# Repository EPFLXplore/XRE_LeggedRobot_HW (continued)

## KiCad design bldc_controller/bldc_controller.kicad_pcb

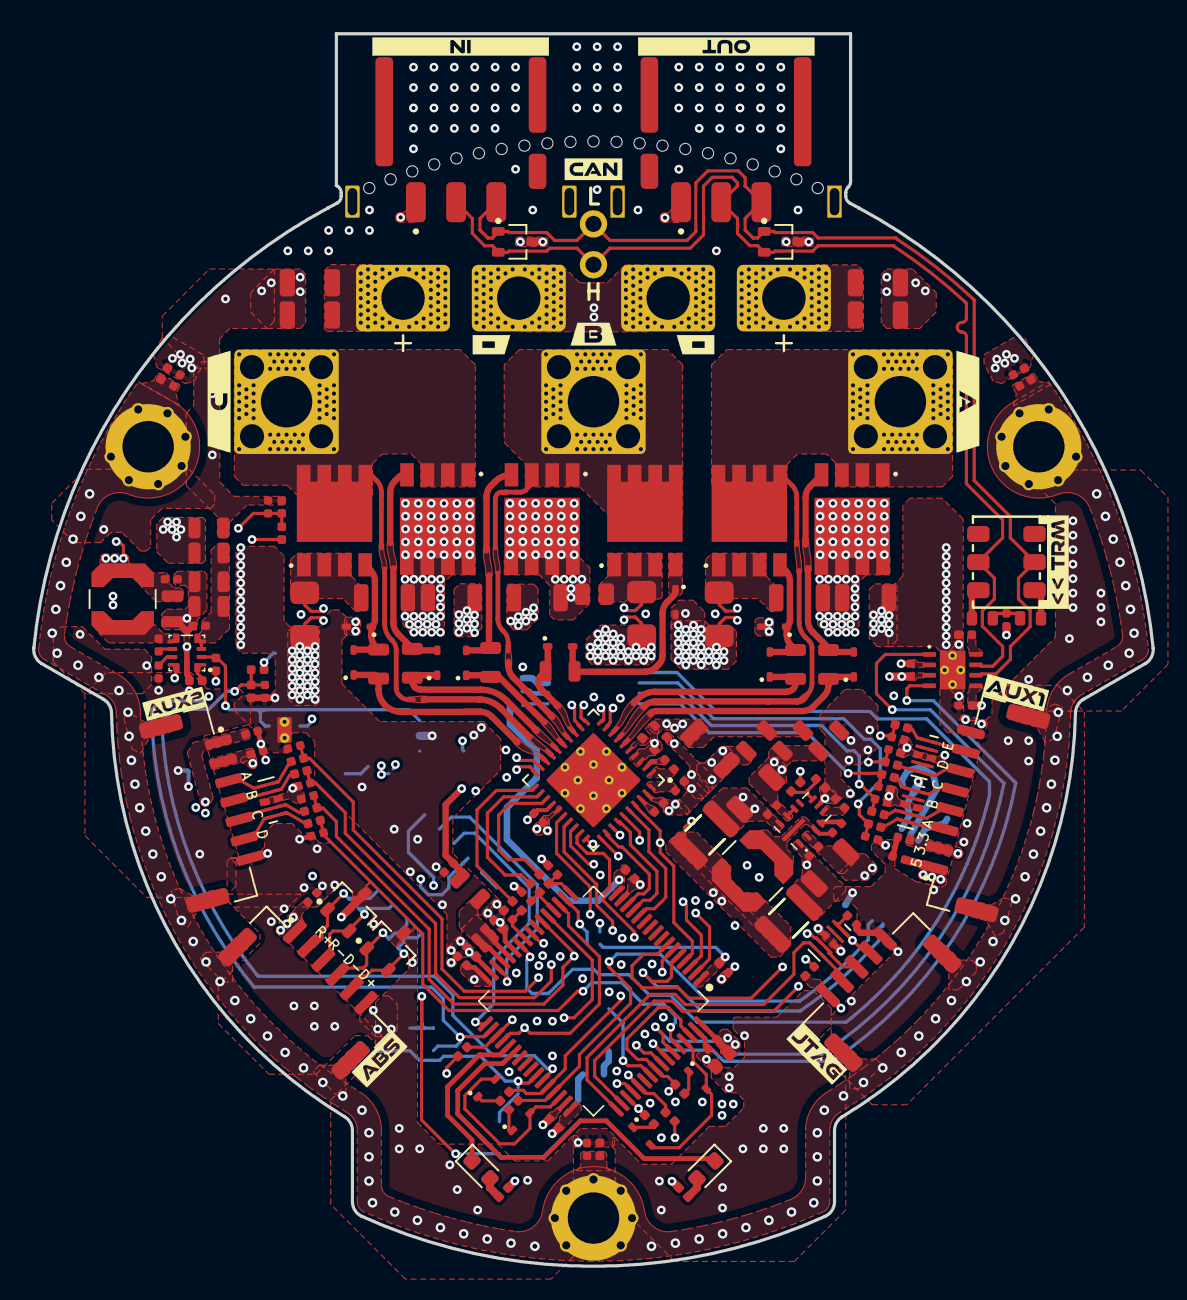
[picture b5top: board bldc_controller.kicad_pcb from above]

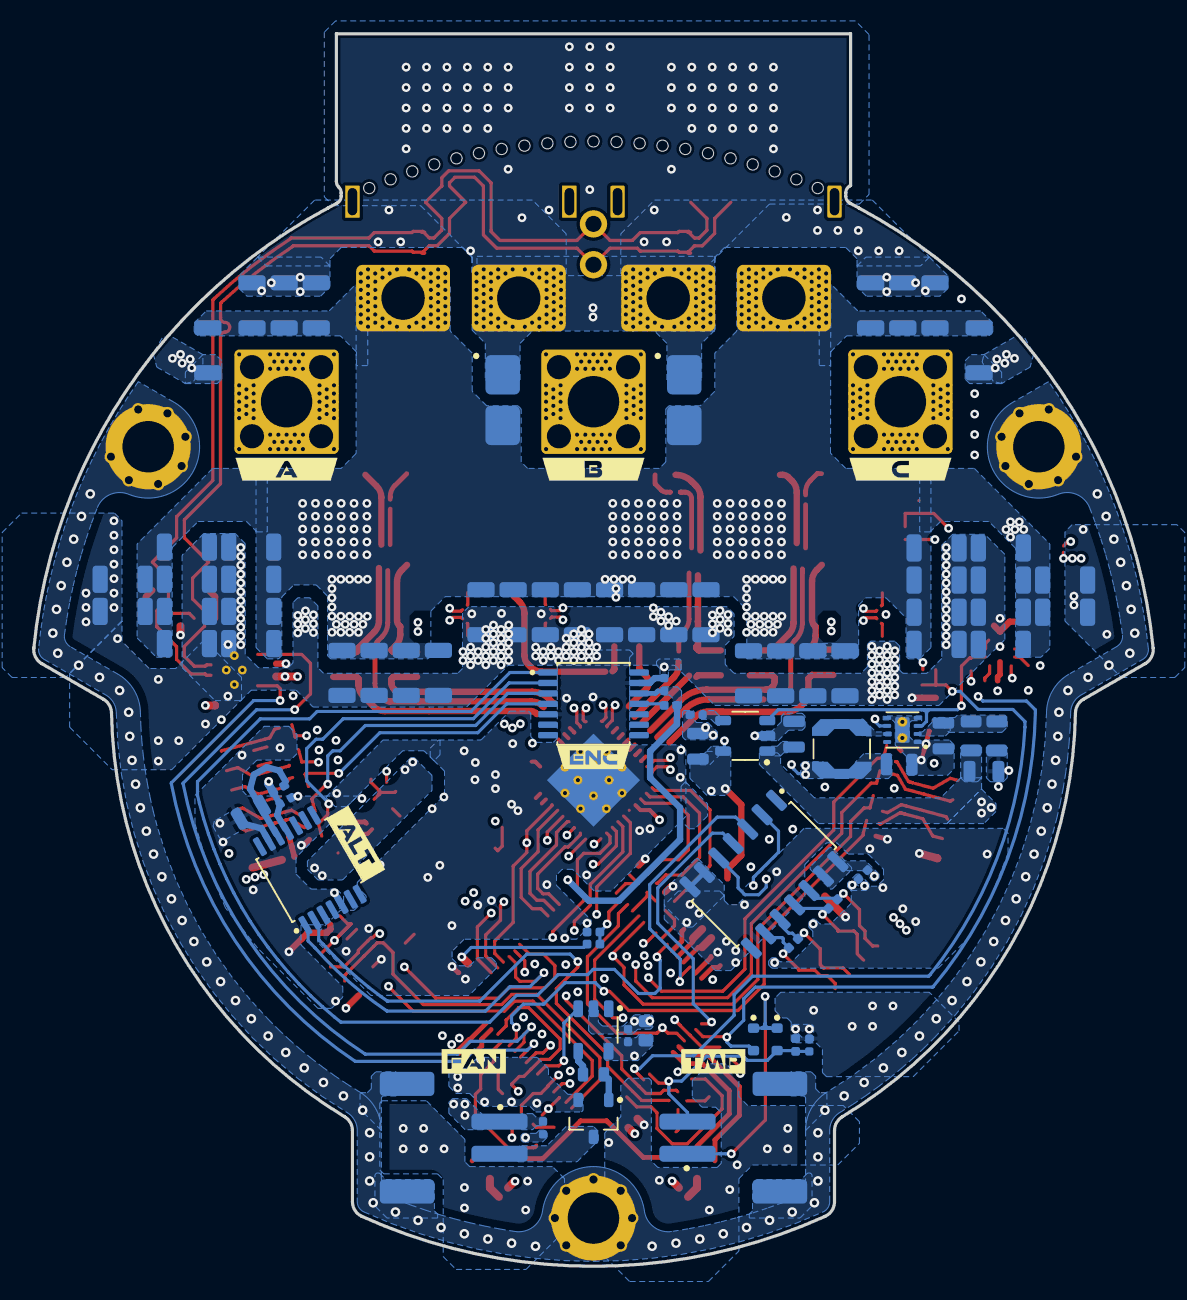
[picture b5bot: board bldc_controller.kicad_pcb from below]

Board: 6 copper layers, 69.7 x 76.7 mm, 287 parts (94 on the bottom side), 131 nets.

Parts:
C1, C103: 4u7 X7R 25V; C_0603_1608_DensityHigh
C2, C3, C6, C8, C9, C10, C54, C58, C79, C80, C94, C95, C96, C98, C99, C100, C101, C102, C104, C105, C106, C107, C108, C118, C123, C131, C132: 100n X7R 100V; C_0402_1005_DensityHigh
C4, C7, C33, C41, C130: 1u X7R 100V; C_0402_1005_DensityHigh
C5, C119: 4u7 X7R 25V; C_0402_1005_DensityHigh
C11, C12, C13: 1n X7R 25V; C_0402_1005_DensityHigh
C14, C15, C16, C18, C19, C20, C21, C22, C23, C24, C25, C26, C27, C28, C30, C31, C32, C34, C35, C36, C38, C39, C40, C42, C43, C44, C45, C46, C47, C48, C49, C50, C51, C52, C53, C55, C56, C57, C59, C60, C61, C63, C64, C65, C66, C67, C68, C70, C71, C72: 4u7 X7R 100V; C_1206_3216_DensityHigh
C17, C124, C125, C126, C127, C128, C129: 2u2 X7R 100V; R_0805_2012_DensityHigh
C29, C37: 220n X7R 100V; C_0402_1005_DensityHigh
C62, C74, C77, C97: 10u X7R 6.3V; C_0805_2012_DensityHighest
C69, C73: 15u X7R 25V; C_1210_3225_DensityHigh
C75: 10u X7R 25V; C_0805_2012_DensityHighest
C76: 10n X7R 25V; C_0402_1005_DensityHigh
C78: 22u X7R 10V; C_0805_2012_DensityHighest
C81: 1u X7R 25V; C_0402_1005_DensitySpaced
C82, C89, C91, C93: 4u7 X7R 100V; C_1206_3216_DensityHighest
C83: 100n X7R 16V; C_0402_1005_DensityHigh
C84: 47n X7R 100V; C_0402_1005_DensityHigh
C85: 100n X7R 100V; C_0402_1005_DensitySpaced
C86: 1u X7R 25V; C_0402_1005_DensityHigh
C87: 1u X7R 16V; C_0402_1005_DensityHigh
C88, C92: 100n X7R 100V; C_1206_3216_DensityHighest
C90: 100n X7R 100V; C_0805_2012_DensityHigh
C109, C110, C111, C112, C113, C114, C115, C116, C117: DNP; C_0402_1005_DensityHigh
C120, C121, C122: 330n X7R 100V; C_0402_1005_DensityHigh
D1, D2, D3, D4, D5, D6, D7, D8, D9, D12, D13, D17, D18, D19, D20: BAT41KFILM; D_SOD-523
D10, D11: GREEN; LED_0603_1608Metric
D14, D15: PESD4USB5B-TTSX; DFN2510-D10
D16, D24: PESD4USB3U-TTSX; DFN2510-D10
D21, D25: CDSOT23-SM712; SOT95P230X117-3N
D22, D23: PESD2CANFD24V-UX; SOT95P230X117-3N
FB1, FB2, FB3, FB4: 1k @ 100MHz; R_0805_2012_DensityHigh
H1, H2, H3: M3; MountingHole_3.2mm_M3_Pad_Via
J1: XT60PW-F; AMASS_XT60PW-F_1x02_P7.20mm_Horizontal
J2: XT60PW-M; AMASS_XT60PW-M_1x02_P7.20mm_Horizontal
J3: Phase A; Pad_Square_Vias_6.5x6.5mm
J4: Phase B; Pad_Square_Vias_6.5x6.5mm
J5: Phase C; Pad_Square_Vias_6.5x6.5mm
J6: SM08B-GHS-TB; JST_GH_SM08B-GHS-TB_1x08-1MP_P1.25mm_Horizontal
J7: SM07B-GHS-TB; JST_GH_SM07B-GHS-TB_1x07-1MP_P1.25mm_Horizontal
J8, J10: JST S2B-PH-SM4-TB; JST_PH_S2B-PH-SM4-TB_1x02-1MP_P2.00mm_Horizontal
J9: SM06B-GHS-TB; JST_GH_SM06B-GHS-TB_1x06-1MP_P1.25mm_Horizontal
J11, J12: Nano-Fit 1x03; 1054301203
J13: SM05B-GHS-TB; JST_GH_SM05B-GHS-TB_1x05-1MP_P1.25mm_Horizontal
J14: PTH 01x02 2.54mm; PTH_1x02_P2.54mm
L1, L2: 22u; L_Coilcraft_LPS4018
L3: 2u2; L_Coilcraft_LPS3314
NT1: FB_5V; NetTie-2_SMD_Pad0.2mm
NT2: FB_12V; NetTie-2_SMD_Pad0.2mm
NT3: VOS_3V3; NetTie-2_SMD_Pad0.2mm
NT4: SRC_HS_A; NetTie-2_SMD_Pad0.3mm
NT5: SHNTA_P; NetTie-2_SMD_Pad0.2mm
NT6: SHNTA_N; NetTie-2_SMD_Pad0.2mm
NT7: SRC_HS_B; NetTie-2_SMD_Pad0.3mm
NT8: SHNTB_P; NetTie-2_SMD_Pad0.2mm
NT9: SHNTB_N; NetTie-2_SMD_Pad0.2mm
NT10: SRC_HS_C; NetTie-2_SMD_Pad0.3mm
NT11: SHNTC_P; NetTie-2_SMD_Pad0.2mm
NT12: SHNTC_N; NetTie-2_SMD_Pad0.2mm
NT13: NTC_MOT_H; NetTie-2_SMD_Pad0.2mm
NT14: NTC_MOT_L; NetTie-2_SMD_Pad0.2mm
Q1, Q2, Q3, Q4, Q5, Q6: TPW1R306PL,L1Q; 2-5S1A
Q7: PMV15ENER; SOT95P230X110-3N
R1, R2, R3: 22R 1%; R_0402_1005_DensityHigh
R4, R26, R27, R47, R48, R49: 0R; R_0402_1005_DensityHigh
R5, R18, R24: 100k 1%; R_0402_1005_DensityHigh
R6: 9k09 1%; R_0402_1005_DensityHigh
R7, R8, R39, R40, R41, R42: 2k 1%; R_0402_1005_DensityHigh
R9, R10, R12, R13, R15, R16: 7R5 1%; R_0805_2012_DensityHigh
R11, R14, R17: 0m5 1% 2W; HCS1206FTL500
R19: DNP; R_0402_1005_DensityHigh
R20, R21: 560R 1%; R_0402_1005_DensityHigh
R22, R23, R28, R50: 10k 1%; R_0402_1005_DensityHigh
R25: 4.7k 1%; R_0402_1005_DensityHigh
R29: 10R 1%; R_0603_1608_DensityHigh
R30, R31, R32, R33, R34, R35, R36, R37, R38, R45, R46: 100R 1%; R_0402_1005_DensityHigh
R43, R44: 60R4 1% 1/4W; R_0603_1608_DensityHigh
SW1: CAS-220TA; CAS-220A_NDC-L
TH1: 47k 1% NTC; R_0402_1005_DensityHigh
U1: STM32G474RET3; LQFP-64_10x10mm_P0.5mm
U2: LMR36503MSC5RPERQ1; LMR36503
U3: LMR36006FSCQRNXRQ1
U4: TPS62172DSG; WSON-8-1EP_2x2mm_P0.5mm_EP0.9x1.6mm_ThermalVias
U5: LP2992IM5-3.3/NOPB; SOT95P280X145-5N
U6, U7: SMBJ51CD-M3/H; DIOM4336X24N
U8: DRV8353FS; WQFN-40-1EP_6x6mm_P0.5mm_EP4.15x4.15mm_ThermalVias
U9: AS5047P; SOP-14_4.4x5mm_P0.65mm_H1.2mm
U10: AS5048B; SOP-14_4.4x5mm_P0.65mm_H1.2mm
U11: SN65HVD35DR; SOIC-14 5.4mm
U12: TCAN1051HGVDRBRQ1; HVSON-8-1EP_3x3mm_P0.65mm_EP1.6x2.4mm_ThermalVias
U13: DGD0216WT-7; SOT-23-5
kibuzzard-657CD0A3: G***; kibuzzard-657CD0A3
kibuzzard-657CD0D0: G***; kibuzzard-657CD0D0
kibuzzard-657CD4CA: G***; kibuzzard-657CD4CA
kibuzzard-657CD4F2: G***; kibuzzard-657CD4F2
kibuzzard-657CD16C: G***; kibuzzard-657CD16C
kibuzzard-657CD27C: G***; kibuzzard-657CD27C
kibuzzard-657CD133: G***; kibuzzard-657CD133
kibuzzard-657CD374: G***; kibuzzard-657CD374
kibuzzard-657CE6B7: G***; kibuzzard-657CE6B7
kibuzzard-657CE6F4: G***; kibuzzard-657CE6F4
kibuzzard-657CE8E9: G***; kibuzzard-657CE8E9
kibuzzard-657CE8F0: G***; kibuzzard-657CE8F0
kibuzzard-657CE9A0: G***; kibuzzard-657CE9A0
kibuzzard-657CE9CF: G***; kibuzzard-657CE9CF
kibuzzard-657CE95C: G***; kibuzzard-657CE95C
kibuzzard-657CE353: G***; kibuzzard-657CE353
kibuzzard-657CE701: G***; kibuzzard-657CE701
kibuzzard-657CE738: G***; kibuzzard-657CE738
kibuzzard-657CEA4F: G***; kibuzzard-657CEA4F
kibuzzard-657CEA6A: G***; kibuzzard-657CEA6A

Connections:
+3V3: C1.1, C2.1, C3.1, C6.1, C7.1, C9.1, C78.1, C79.1, C80.1, C99.1, C100.1, C101.1, C107.1, C108.1, J6.2, J7.2, J13.1, L3.2, NT3.2, R7.1, R8.1, R18.1, R20.1, R21.1, R26.1, R27.1, U1.1 (VBAT), U1.16 (VDD), U1.32 (VDD), U1.48 (VDD), U1.64 (VDD), U9.12 (VDD3V3), U10.11 (VDD5V), U11.13 (VCC), U11.14 (VCC), U12.5 (VIO)
+5V: C54.1, C62.1, C74.1, C98.1, C102.1, C103.1, C104.1, C105.1, C106.1, C125.1, FB3.1, J6.1, J7.1, J9.1, L1.2, NT1.1, R50.2, U5.1 (VIN), U12.3 (VCC), U13.5 (VCC)
+12V: C69.1, C73.1, C123.1, J10.1, L2.2, NT2.2
+A3V3: C77.1, C83.1, C130.1, D12.1 (K), D13.1 (K), FB4.1, NT13.1, TH1.1, U5.5 (VOUT), U8.24 (VREF)
+VBAT: C14.1, C15.1, C16.1, C19.1, C20.1, C21.1, C22.1, C23.1, C24.1, C26.1, C27.1, C28.1, C30.1, C31.1, C32.1, C34.1, C35.1, C36.1, C38.1, C39.1, C40.1, C42.1, C43.1, C44.1, C45.1, C46.1, C47.1, C48.1, C49.1, C50.1, C51.1, C52.1, C53.1, C55.1, C56.1, C57.1, C59.1, C60.1, C61.1, C63.1, C64.1, C65.1, C66.1, C67.1, C68.1, C70.1, C71.1, C72.1, C81.1, C82.1, C85.1, C88.1, C89.1, C90.1, C91.1, C92.1, C93.1, C127.1, C128.1, FB1.1, FB2.1, J1.2, J2.2, Q1.5 (D), Q1.6 (D), Q1.7 (D), Q1.8 (D), Q3.5 (D), Q3.6 (D), Q3.7 (D), Q3.8 (D), Q5.5 (D), Q5.6 (D), Q5.7 (D), Q5.8 (D), R24.1, U6.2 (A2), U7.2 (A2), U8.3 (VM), U8.4 (VDRAIN)
/Project Architecture/Interface - FD-CAN/FDCAN_N: D22.1 (K1), D23.1 (K1), J11.3, J12.3, J14.2, SW1.2 (B), U12.6 (CANL)
/Project Architecture/Interface - FD-CAN/FDCAN_P: D22.2 (K2), D23.2 (K2), J11.2, J12.2, J14.1, SW1.5 (B), U12.7 (CANH)
/Project Architecture/Interface - FD-CAN/FDCAN_RX: U1.58 (PB5), U12.4 (RXD)
/Project Architecture/Interface - FD-CAN/FDCAN_S: R28.1, U12.8 (S)
/Project Architecture/Interface - FD-CAN/FDCAN_TX: U1.59 (PB6), U12.1 (TXD)
/Project Architecture/Interface - Fan Control/FAN_GATE: Q7.1 (G), R29.2
/Project Architecture/Interface - Fan Control/FAN_OUT: R29.1, U13.4 (OUT)
/Project Architecture/Interface - Fan Control/FAN_SW: J10.2, Q7.3 (D)
/Project Architecture/Interface - Interconnects/AUX1P_A: D16.5 (K), D16.6 (K), J6.3, R30.1
/Project Architecture/Interface - Interconnects/AUX1P_B: D16.4 (K), D16.7 (K), J6.4, R31.1
/Project Architecture/Interface - Interconnects/AUX1P_C: D16.1 (K), D16.10 (K), J6.5, R32.1
/Project Architecture/Interface - Interconnects/AUX1P_D: D14.5 (K), D14.6 (K), J6.6, R33.1
/Project Architecture/Interface - Interconnects/AUX1P_E: D14.1 (K), D14.10 (K), J6.7, R34.1
/Project Architecture/Interface - Interconnects/AUX1_A: C117.1, R30.2, U1.19 (PA5), U1.36 (PB14), U9.2 (CLK)
/Project Architecture/Interface - Interconnects/AUX1_B: C115.1, R31.2, U1.57 (PB4), U9.3 (MISO)
/Project Architecture/Interface - Interconnects/AUX1_C: C113.1, R32.2, U1.21 (PA7), U9.4 (MOSI)
/Project Architecture/Interface - Interconnects/AUX1_D: C111.1, R33.2, R39.2, U1.51 (PA15), U11.2 (R)
/Project Architecture/Interface - Interconnects/AUX1_D_K: D17.1 (K), R39.1
/Project Architecture/Interface - Interconnects/AUX1_E: C109.1, R34.2, R41.2, U1.56 (PB3), U1.62 (PB9), U11.5 (D)
/Project Architecture/Interface - Interconnects/AUX1_E_K: D19.1 (K), R41.1
/Project Architecture/Interface - Interconnects/AUX1_I2C_PULLUP: D17.2 (A), D19.2 (A), U1.61 (PB8)
/Project Architecture/Interface - Interconnects/AUX2P_A: D15.5 (K), D15.6 (K), J7.3, R35.1
/Project Architecture/Interface - Interconnects/AUX2P_B: D15.4 (K), D15.7 (K), J7.4, R36.1
/Project Architecture/Interface - Interconnects/AUX2P_C: D15.2 (K), D15.9 (K), J7.5, R37.1
/Project Architecture/Interface - Interconnects/AUX2P_D: D15.1 (K), D15.10 (K), J7.6, R38.1
/Project Architecture/Interface - Interconnects/AUX2_A: C116.1, R35.2, U1.6 (PF1)
/Project Architecture/Interface - Interconnects/AUX2_B: C114.1, R36.2, R40.2, U1.5 (PF0), U1.44 (PA10), U10.1 (SDA)
/Project Architecture/Interface - Interconnects/AUX2_B_K: D18.1 (K), R40.1
/Project Architecture/Interface - Interconnects/AUX2_C: C112.1, R37.2, R42.2, U1.22 (PC4), U1.45 (PA11), U10.2 (SCL)
/Project Architecture/Interface - Interconnects/AUX2_C_K: D20.1 (K), R42.1
/Project Architecture/Interface - Interconnects/AUX2_D: C110.1, R38.2, U1.60 (PB7)
/Project Architecture/Interface - Interconnects/AUX2_I2C_PULLUP: D18.2 (A), D20.2 (A), U1.46 (PA12)
/Project Architecture/Interface - Interconnects/CAN_TERM_B: R44.2, SW1.4 (A)
/Project Architecture/Interface - Interconnects/CAN_TERM_MID: C119.1, R43.2, R44.1
/Project Architecture/Interface - Interconnects/CAN_TERM_T: R43.1, SW1.1 (A)
/Project Architecture/Interface - Interconnects/NRST: C118.1, D24.1 (K), D24.10 (K), J13.4, U1.7 (PG10)
/Project Architecture/Interface - Interconnects/NTC_MOT_H: J8.1, NT13.2
/Project Architecture/Interface - Interconnects/NTC_MOT_L: J8.2, NT14.2
/Project Architecture/Interface - Interconnects/POS_SENSOR_CS: U1.26 (PB2), U9.1 (~CS)
/Project Architecture/Interface - Interconnects/RS422_D+: D21.2 (A2), J9.5, R46.2, U11.9 (Y)
/Project Architecture/Interface - Interconnects/RS422_D-: D21.1 (A1), J9.4, R46.1, U11.10 (Z)
/Project Architecture/Interface - Interconnects/RS422_R+: D25.1 (A1), J9.2, R45.1, U11.12 (A)
/Project Architecture/Interface - Interconnects/RS422_R-: D25.2 (A2), J9.3, R45.2, U11.11 (B)
/Project Architecture/Interface - Interconnects/SWCLK: D24.4 (K), D24.7 (K), J13.3, U1.50 (PA14)
/Project Architecture/Interface - Interconnects/SWDIO: D24.5 (K), D24.6 (K), J13.2, U1.49 (PA13)
/Project Architecture/Interface - RS-422/RS422_DE: U1.33 (PB11), U11.4 (DE)
/Project Architecture/Interface - RS-422/RS422_~RE: U1.30 (PB10), U11.3 (~RE)
/Project Architecture/MCU - IOs/BOARD_VERSION: R18.2, R19.1, U1.18 (PA4)
/Project Architecture/MCU - IOs/DRV_CS: U1.24 (PB0), U8.30 (nSCS)
/Project Architecture/MCU - IOs/DRV_MISO: R8.2, U1.53 (PC11), U8.27 (SDO)
/Project Architecture/MCU - IOs/DRV_MOSI: U1.2 (PC13), U8.28 (SDI)
/Project Architecture/MCU - IOs/DRV_SCLK: U1.52 (PC10), U8.29 (SCLK)
/Project Architecture/MCU - IOs/FAN_CTRL: U1.55 (PD2), U13.3 (IN)
/Project Architecture/MCU - IOs/FILTER_SOA: C11.1, R1.1, U1.17 (PA3)
/Project Architecture/MCU - IOs/FILTER_SOB: C12.1, R2.1, U1.20 (PA6)
/Project Architecture/MCU - IOs/FILTER_SOC: C13.1, R3.1, U1.25 (PB1)
/Project Architecture/MCU - IOs/LED1: D10.1 (K), U1.37 (PB15)
/Project Architecture/MCU - IOs/LED2: D11.1 (K), U1.38 (PC6)
/Project Architecture/MCU - IOs/MOTOR_ENABLE: U1.3 (PC14), U8.31 (ENABLE)
/Project Architecture/MCU - IOs/MOTOR_FAULT: R7.2, U1.35 (PB13), U8.26 (nFAULT)
/Project Architecture/MCU - IOs/MOTOR_HIZ: U1.4 (PC15), U8.33 (INLA), U8.35 (INLB), U8.37 (INLC)
/Project Architecture/MCU - IOs/PWM_PHASEA: U1.14 (PA2), U8.32 (INHA)
/Project Architecture/MCU - IOs/PWM_PHASEB: U1.13 (PA1), U8.34 (INHB)
/Project Architecture/MCU - IOs/PWM_PHASEC: U1.12 (PA0), U8.36 (INHC)
/Project Architecture/MCU - IOs/SENSE_TEMP_FET: C94.1, D12.2 (A), R22.1, TH1.2, U1.34 (PB12)
/Project Architecture/MCU - IOs/SENSE_TEMP_MOT: C95.1, D13.2 (A), NT14.1, R23.1, U1.42 (PA8)
/Project Architecture/MCU - IOs/SENSE_VBAT: C96.1, R24.2, R25.1, U1.43 (PA9)
/Project Architecture/MCU - IOs/SOA: R1.2, U8.23 (SOA)
/Project Architecture/MCU - IOs/SOB: R2.2, U8.22 (SOB)
/Project Architecture/MCU - IOs/SOC: R3.2, U8.21 (SOC)
/Project Architecture/MCU - Power/F_A3V3: C4.1, C5.1, C8.1, C10.1, FB4.2, U1.28 (VREF+), U1.29 (VDDA)
/Project Architecture/Motor Control - Top Level/CPH: C84.1, U8.2 (CPH)
/Project Architecture/Motor Control - Top Level/CPL: C84.2, U8.1 (CPL)
/Project Architecture/Motor Control - Top Level/DVDD: C87.1, U8.38 (DVDD)
/Project Architecture/Motor Control - Top Level/GHA: D2.1 (K), R9.2, U8.6 (GHA)
/Project Architecture/Motor Control - Top Level/GHB: D5.1 (K), R12.1, U8.15 (GHB)
/Project Architecture/Motor Control - Top Level/GHC: D8.1 (K), R15.1, U8.16 (GHC)
/Project Architecture/Motor Control - Top Level/GLA: D3.1 (K), R10.1, U8.8 (GLA)
/Project Architecture/Motor Control - Top Level/GLB: D6.1 (K), R13.1, U8.13 (GLB)
/Project Architecture/Motor Control - Top Level/GLC: D9.1 (K), R16.1, U8.18 (GLC)
/Project Architecture/Motor Control - Top Level/Motor Control - Inverter/FET_GHA: D2.2 (A), Q1.4 (G), R9.1
/Project Architecture/Motor Control - Top Level/Motor Control - Inverter/FET_GHB: D5.2 (A), Q3.4 (G), R12.2
/Project Architecture/Motor Control - Top Level/Motor Control - Inverter/FET_GHC: D8.2 (A), Q5.4 (G), R15.2
/Project Architecture/Motor Control - Top Level/Motor Control - Inverter/FET_GLA: D1.1 (K), D3.2 (A), Q2.4 (G), R10.2
/Project Architecture/Motor Control - Top Level/Motor Control - Inverter/FET_GLB: D4.1 (K), D6.2 (A), Q4.4 (G), R13.2
/Project Architecture/Motor Control - Top Level/Motor Control - Inverter/FET_GLC: D7.1 (K), D9.2 (A), Q6.4 (G), R16.2
/Project Architecture/Motor Control - Top Level/Motor Control - Inverter/PHA: J3.1, NT4.2, Q1.1 (S), Q1.2 (S), Q1.3 (S), Q2.5 (D), Q2.6 (D), Q2.7 (D), Q2.8 (D)
/Project Architecture/Motor Control - Top Level/Motor Control - Inverter/PHB: J4.1, NT7.2, Q3.1 (S), Q3.2 (S), Q3.3 (S), Q4.5 (D), Q4.6 (D), Q4.7 (D), Q4.8 (D)
/Project Architecture/Motor Control - Top Level/Motor Control - Inverter/PHC: J5.1, NT10.2, Q5.1 (S), Q5.2 (S), Q5.3 (S), Q6.5 (D), Q6.6 (D), Q6.7 (D), Q6.8 (D)
/Project Architecture/Motor Control - Top Level/Motor Control - Inverter/SRC_LS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: C88.2, NT5.1, Q2.1 (S), Q2.2 (S), Q2.3 (S), R11.2
/Project Architecture/Motor Control - Top Level/Motor Control - Inverter/SRC_LS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: C90.2, NT8.2, Q4.1 (S), Q4.2 (S), Q4.3 (S), R14.2
/Project Architecture/Motor Control - Top Level/Motor Control - Inverter/SRC_LS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: C92.2, NT11.2, Q6.1 (S), Q6.2 (S), Q6.3 (S), R17.2
/Project Architecture/Motor Control - Top Level/SA_N: NT6.1, U8.10 (SNA)
/Project Architecture/Motor Control - Top Level/SA_P: NT5.2, U8.9 (SPA)
/Project Architecture/Motor Control - Top Level/SB_N: NT9.1, U8.11 (SNB)
/Project Architecture/Motor Control - Top Level/SB_P: NT8.1, U8.12 (SPB)
/Project Architecture/Motor Control - Top Level/SC_N: NT12.1, U8.20 (SNC)
/Project Architecture/Motor Control - Top Level/SC_P: NT11.1, U8.19 (SPC)
/Project Architecture/Motor Control - Top Level/SHA: NT4.1, U8.7 (SHA)
/Project Architecture/Motor Control - Top Level/SHB: NT7.1, U8.14 (SHB)
/Project Architecture/Motor Control - Top Level/SHC: NT10.1, U8.17 (SHC)
/Project Architecture/Motor Control - Top Level/VCP: C81.2, U8.5 (VCP)
/Project Architecture/Motor Control - Top Level/VGLS: C86.1, U8.40 (VGLS)
/Project Architecture/Power - Generation/ADJ_A3V3: C76.1, U5.4 (ADJ)
/Project Architecture/Power - Generation/BOOT_5V: C131.2, U2.6 (BOOT)
/Project Architecture/Power - Generation/BOOT_12V: C58.2, U3.4 (BOOT)
/Project Architecture/Power - Generation/FB_5V: NT1.2, U2.8 (FB)
/Project Architecture/Power - Generation/FB_12V: NT2.1, R5.1
/Project Architecture/Power - Generation/FB_DIV_12V: R5.2, R6.1, U3.7 (FB)
/Project Architecture/Power - Generation/F_VIN_3V3: C75.1, C124.1, FB3.2, U4.2 (VIN)
/Project Architecture/Power - Generation/F_VIN_5V: C17.1, C129.1, C132.1, FB2.2, U2.3 (EN/UVLO), U2.4 (VIN)
/Project Architecture/Power - Generation/F_VIN_12V: C18.1, C25.1, C29.1, C37.1, C126.1, FB1.2, U3.2 (VIN), U3.9 (EN), U3.10 (VIN)
/Project Architecture/Power - Generation/MODE_5V: R4.1, U2.1 (MODE/SYNC)
/Project Architecture/Power - Generation/PG_5V: R50.1, U2.2 (PGOOD), U4.3 (EN), U5.3 (ON/~OFF)
/Project Architecture/Power - Generation/SW_3V3: L3.1, U4.7 (SW)
/Project Architecture/Power - Generation/SW_5V: C131.1, L1.1, U2.5 (SW)
/Project Architecture/Power - Generation/SW_12V: C58.1, L2.1, U3.3 (NC), U3.12 (SW)
/Project Architecture/Power - Generation/VCC_5V: C33.1, U2.7 (VCC)
/Project Architecture/Power - Generation/VCC_12V: C41.1, U3.5 (VCC)
/Project Architecture/Power - Generation/VOS_3V3: NT3.1, U4.6 (VOS)
/Project Architecture/Sensing - Position/COMM_VDD: R26.2, U9.11 (VDD)
/Project Architecture/Sensing - Position/DIS_VDD3V: C97.1, R27.2, U10.12 (VDD3V)
/Project Architecture/User - LED Indicators/LED1_A: D10.2 (A), R20.2
/Project Architecture/User - LED Indicators/LED2_A: D11.2 (A), R21.2
CHASSIS: C120.1, C121.1, C122.1, H1.1, H2.1, H3.1, J6.MP, J7.MP, J8.MP, J9.MP, J10.MP, J13.MP, R47.1, R48.1, R49.1
GND: C1.2, C2.2, C3.2, C4.2, C5.2, C6.2, C7.2, C8.2, C9.2, C10.2, C11.2, C12.2, C13.2, C14.2, C15.2, C16.2, C17.2, C18.2, C19.2, C20.2, C21.2, C22.2, C23.2, C24.2, C25.2, C26.2, C27.2, C28.2, C29.2, C30.2, C31.2, C32.2, C33.2, C34.2, C35.2, C36.2, C37.2, C38.2, C39.2, C40.2, C41.2, C42.2, C43.2, C44.2, C45.2, C46.2, C47.2, C48.2, C49.2, C50.2, C51.2, C52.2, C53.2, C54.2, C55.2, C56.2, C57.2, C59.2, C60.2, C61.2, C62.2, C63.2, C64.2, C65.2, C66.2, C67.2, C68.2, C69.2, C70.2, C71.2, C72.2, C73.2, C74.2, C75.2, C76.2, C77.2, C78.2, C79.2, C80.2, C82.2, C83.2, C85.2, C86.2, C87.2, C89.2, C91.2, C93.2, C94.2, C95.2, C96.2, C97.2, C98.2, C99.2, C100.2, C101.2, C102.2, C103.2, C104.2, C105.2, C106.2, C107.2, C108.2, C109.2, C110.2, C111.2, C112.2, C113.2, C114.2, C115.2, C116.2, C117.2, C118.2, C119.2, C120.2, C121.2, C122.2, C123.2, C124.2, C125.2, C126.2, C127.2, C128.2, C129.2, C130.2, C132.2, D1.2 (A), D4.2 (A), D7.2 (A), D14.3 (A), D14.8 (A), D15.3 (A), D15.8 (A), D16.3 (A), D16.8 (A), D21.3 (common), D22.3 (CC), D23.3 (CC), D24.3 (A), D24.8 (A), D25.3 (common), J1.1, J2.1, J6.8, J7.7, J9.6, J11.1, J12.1, J13.5, NT6.2, NT9.2, NT12.2, Q7.2 (S), R4.2, R6.2, R11.1, R14.1, R17.1, R19.2, R22.2, R23.2, R25.2, R28.2, R47.2, R48.2, R49.2, U1.15 (VSS), U1.27 (VSSA), U1.31 (VSS), U1.47 (VSS), U1.63 (VSS), U2.9 (GND), U3.1 (PGND), U3.6 (AGND), U3.11 (PGND), U4.1 (PGND), U4.4 (AGND), U4.5 (FB), U4.9 (PAD), U5.2 (GND), U6.1 (A1), U7.1 (A1), U8.25 (AGND), U8.39 (GND), U8.41 (EP), U9.5 (TST), U9.13 (GND), U10.5 (TEST), U10.13 (GND), U11.6 (GND), U11.7 (GND), U12.2 (GND), U12.9 (PAD), U13.2 (COM)

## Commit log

2023-10-12 added empty project
2023-10-15 first commit, schematic not complete yet
2023-10-16 some progress
2023-10-23 added temporary footprints and deleted extra files
2023-10-23 updated .gitignore
2023-10-23 added temporary schematic and resolved off-grid connections
2023-10-23 removed plots
2023-10-23 added temporary pdf plot
2023-11-04 added IPC-7351 compliant footprints and started routing
2023-11-12 some progress on the pcb
2023-11-14 routed CAN, added new footprints
2023-11-15 added 12V buck
2023-11-17 routed 12V buck. Need to change mcu package and add fan low-side switch
2023-11-17 minor changes before changing mcu
2023-11-19 added power domains. Risk of ground shift near CAN
2023-11-21 Added TVS diodes to all interfaces
2023-11-26 might have fixed net issue, added dxf and svgs
2023-11-26 added chassis connection to connector MP. Might need to change design rules to be compatible with low-cost PCBWay
2023-11-27 starting rerouting for PCBWay 8/8 mils, 0.25mm drill
2023-11-28 added mousebites, custom footprints and routed some digital/analog parts
2023-11-29 routed most digital signals. Need to reroute power planes (keep good reference above and below analog signals)
2023-12-01 Replaced 3v3 buck with WSON package alternative. Will back-annotate components
2023-12-02 routed all signals. TODO: redo all power polygons and ensure good return paths/reference. Added 3d models
2023-12-04 started routing polygons
2023-12-06 TODO: reroute power stage
2023-12-08 Added block diagram, currently rerouting power polygons
2023-12-08 updated schematic
2023-12-10 finished most of routing. Need to add testpoints and clean up graphics
2023-12-11 finished routing. Replacing components with IPC7351 compliant footprints generated in altium
2023-12-14 schematic is complete. Replaced 5V buck and added pi filters.
2023-12-16 added assembly files
2023-12-16 updated .gitignore:
2023-12-16 renamed project
2023-12-17 filled in fields for bom, replaced inexisting components. Need to replace LEDs
2023-12-19 added test points
2023-12-20 finalized pcb. TODO: add clean BOM and KiBot integration
2023-12-20 minor updates
2023-12-20 added assembly doc
2023-12-20 fixed weird compression
2023-12-20 fixed page order:
2023-12-20 added 2d renders to assembly files
2023-12-20 fixed copper pour on front layer
2023-12-20 removed unused file
2023-12-20 reduced file size
2023-12-20 fixed wrong layer stackup information on layer 2
2023-12-20 fixed clearance between chassis and GND around connector MP
2023-12-20 fixed spacing between chassis and GND on back layer on MP pads
2023-12-20 fixed wrong copper layer on back testpoint plot
2023-12-20 fixed wrong page order
2023-12-20 small typos
2023-12-21 minor drc errors fixed
2023-12-21 fixed 6p connector symbol
2023-12-21 fixed bad masking on back render
2023-12-21 hide 3d models for DNP parts
2023-12-23 updated documents
2023-12-23 removed GND label from LED sheet
2023-12-23 fixed units in bottom dimensions + missing line in stackup drawing
2023-12-30 corrected pcb according to reviews on reddit
2023-12-31 ci/cd test with kibot (quickstart)
2023-12-31 deleted gha
2023-12-31 added BOM, gerbers, position files, assembly document and new schematic pdf
2023-12-31 corrected gerber extension in stackup legend
2023-12-31 small typo
2023-12-31 fixed block diagram LED voltage
2024-01-01 typo in testpoint name
2024-01-03 Fixed clearance between +VBAT via and GND
2024-01-03 fixed net colors for RC snubber
2024-01-03 removed old images
2024-01-03 renamed folders
2024-01-03 updated step
2024-01-03 renamed folder
2024-01-24 finished routing new version of amulet. Need to prepare assembly docs/bom
2024-01-25 added fabrication and assembly files
2024-01-26 small fixes
2024-03-01 Added Project
2024-03-12 modified power sequencing graph and added encoder schematic
2024-03-18 Create LICENSE
2024-03-18 Added picture of amulet
2024-03-18 Added more pictures of amulet
2024-03-18 Added light version of logo
2024-03-18 Update README.md with dark mode logo
2024-03-21 preliminary layout
2024-03-27 Buck module finished pending review
2024-04-01 preliminary routing of encoder
2024-04-01 added silkscreen, better routing
2024-04-01 Correction module
2024-04-13 Rev 1.0 of smps finished -> waiting for verification
2024-04-14 amulet v1.1 released
2024-04-14 updated 3d models
2024-04-14 removed unused files
2024-04-14 fixed bad image quality in assembly file
2024-04-14 removed autosave files
2024-04-19 Little change, ready to order
2024-04-23 updated html bom with rev1.1
2024-05-04 Geode test board ready to order
2024-05-06 rough version of encoder
2024-05-18 done !!:s^
2024-10-14 testing kibot workflow
2024-10-15 testing generation of CSV and KiCost BOM
2024-10-15 added generated kicost bom
2024-10-16 assembly top pcb print
2024-10-16 test pcb print: bug with footprint hole color
2024-10-16 hole color bug test cases
2024-10-31 close to fully automated workflow
2024-11-12 automation of pcb renders
2024-11-12 Added few outputs to kibot config
2024-11-12 minor changes in kibot config
2024-11-12 ignore identifier files
2024-11-14 draft of kibot config files. Need to add text variables
2024-11-14 added comments
2024-11-15 Added bash script for multiple kibot runs
2024-11-15 change kibot output dir
2024-11-15 Do not move files with compression
2024-11-15 use correct filter for assembly
2024-11-15 Changed title location
2024-11-19 Added git hash parsing
2024-11-21 KiCost test
2024-11-21 Better syntax for fab copper layers and testpoints
2024-11-21 Stay compatible with current dev branch of kibot
2024-11-23 test CI
2024-11-26 fix body in release
